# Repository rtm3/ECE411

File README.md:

ECE411 - T03
======

Group Design Project

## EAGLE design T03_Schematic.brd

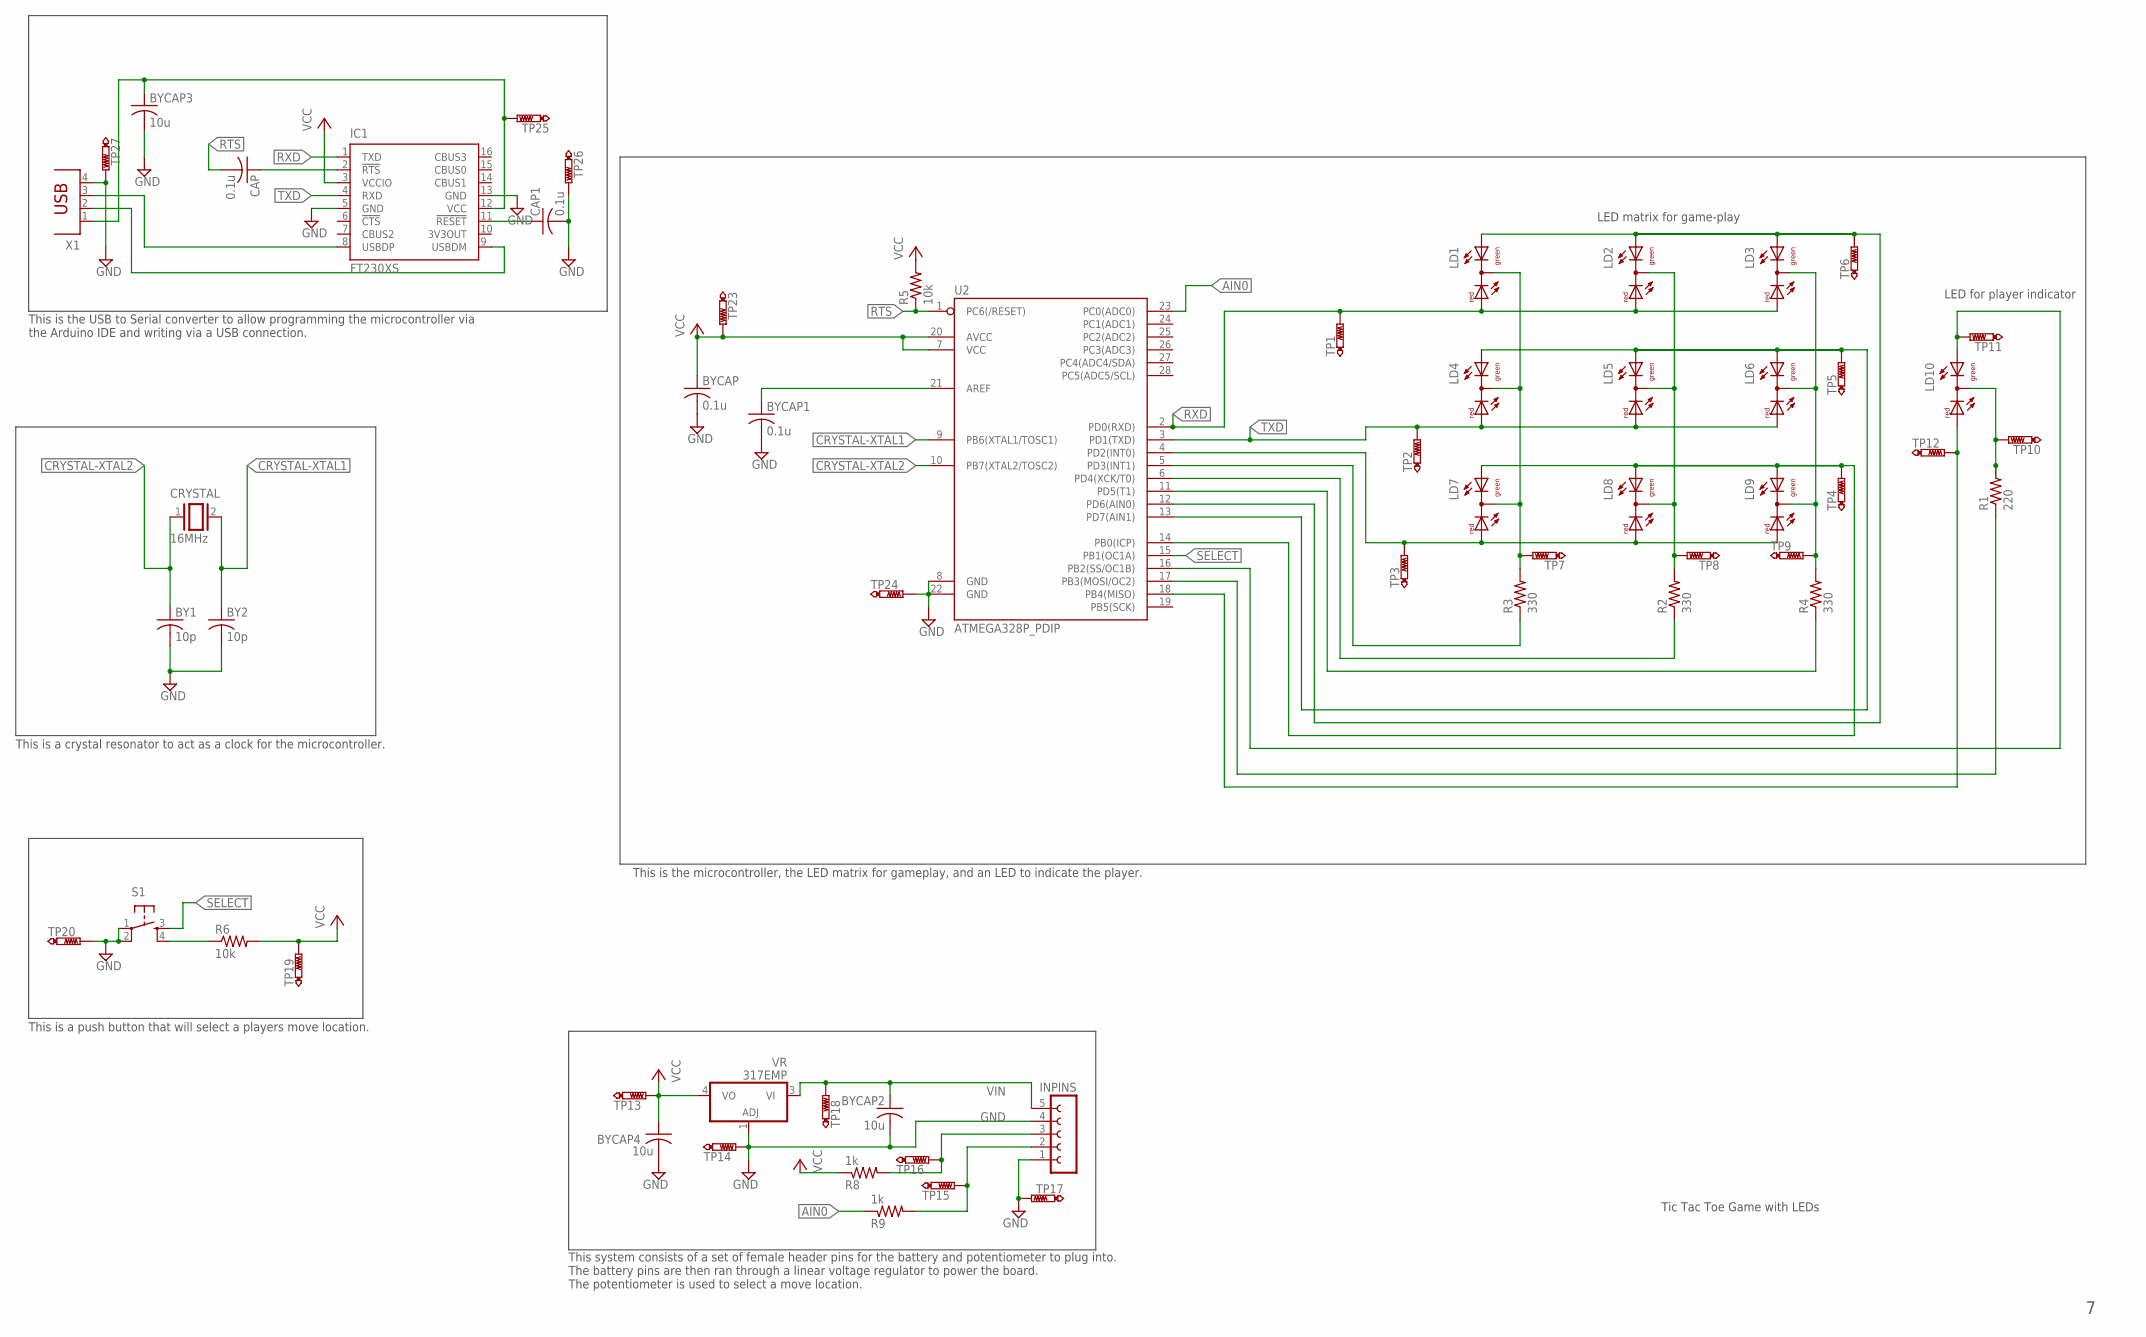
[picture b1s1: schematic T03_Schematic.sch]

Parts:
BY1, BY2: 10p; C0805
BYCAP, BYCAP1: 0.1u; C0805
BYCAP2, BYCAP3, BYCAP4: 10u; C0805
CAP, CAP1: 0.1u; C0805
CRYSTAL: 16MHz; QS
IC1: FT230XS; SSOP16
INPINS: FE05-1
LD1, LD2, LD3, LD4, LD5, LD6, LD7, LD8, LD9, LD10: DUOLED-RG-C; DUOLED-C-5MM
R1: 220; M0805
R2, R3, R4: 330; M0805
R5, R6: 10k; M0805
R8, R9: 1k; M0805
S1: DTS-6
TP1, TP2, TP3, TP4, TP5, TP6, TP7, TP8, TP9, TP10, TP11, TP12, TP13, TP14, TP15, TP16, TP17, TP18, TP19, TP20, TP23, TP24, TP25, TP26, TP27: PTR1B1,27; B1,27
U2: ATMEGA328P_PDIP; DIL28-3
VR: 317EMP; SOT223
X1: PN61729

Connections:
AIN0: R9.1, U2.23 (PC0(ADC0))
CATH1: R3.1, U2.5 (PD3(INT1))
CATH2: R2.1, U2.6 (PD4(XCK/T0))
CATH3: R4.1, U2.11 (PD5(T1))
CATH4: R1.1, U2.17 (PB3(MOSI/OC2))
CRYSTAL-XTAL1: BY2.1, CRYSTAL.2, U2.9 (PB6(XTAL1/TOSC1))
CRYSTAL-XTAL2: BY1.1, CRYSTAL.1, U2.10 (PB7(XTAL2/TOSC2))
D+: IC1.8 (USBDP), X1.3
D-: IC1.9 (USBDM), X1.2
GND: BY1.2, BY2.2, BYCAP.2, BYCAP1.2, BYCAP2.2, BYCAP3.2, BYCAP4.2, CAP1.2, IC1.5 (GND), IC1.13 (GND), INPINS.1, INPINS.4, S1.1, S1.2, TP14.TP, TP17.TP, TP20.TP, TP24.TP, TP26.TP, TP27.TP, U2.8 (GND), U2.22 (GND), VR.1 (ADJ), X1.4
GREN1: LD1.AX (AG), LD2.AX (AG), LD3.AX (AG), TP6.TP, U2.12 (PD6(AIN0))
GREN2: LD4.AX (AG), LD5.AX (AG), LD6.AX (AG), TP5.TP, U2.13 (PD7(AIN1))
GREN3: LD7.AX (AG), LD8.AX (AG), LD9.AX (AG), TP4.TP, U2.14 (PB0(ICP))
unnamed: LD1.C, LD4.C, LD7.C, R3.2, TP7.TP
unnamed: R6.1, S1.4
unnamed: LD2.C, LD5.C, LD8.C, R2.2, TP8.TP
unnamed: CAP.1, IC1.2 (!RTS)
unnamed: LD3.C, LD6.C, LD9.C, R4.2, TP9.TP
unnamed: CAP1.1, IC1.11 (!RESET)
unnamed: BYCAP1.1, U2.21 (AREF)
unnamed: LD10.C, R1.2, TP10.TP
PLAY1: LD10.AX (AG), TP11.TP, U2.16 (PB2(SS/OC1B))
PLAY2: LD10.AR, TP12.TP, U2.18 (PB4(MISO))
RED3: LD7.AR, LD8.AR, LD9.AR, TP3.TP, U2.4 (PD2(INT0))
RTS: CAP.2, R5.1, U2.1 (PC6(/RESET))
RXD: IC1.1 (TXD), LD1.AR, LD2.AR, LD3.AR, TP1.TP, U2.2 (PD0(RXD))
SELECT: S1.3, U2.15 (PB1(OC1A))
SELECTPIN: INPINS.2, R9.2, TP15.TP
TXD: IC1.4 (RXD), LD4.AR, LD5.AR, LD6.AR, TP2.TP, U2.3 (PD1(TXD))
USBVCC: BYCAP3.1, IC1.12 (VCC), TP25.TP, X1.1
V+POT: INPINS.3, R8.2, TP16.TP
VCC: BYCAP.1, BYCAP4.1, IC1.3 (VCCIO), R5.2, R6.2, R8.1, TP13.TP, TP19.TP, TP23.TP, U2.7 (VCC), U2.20 (AVCC), VR.4 (VO)
VIN: BYCAP2.1, INPINS.5, TP18.TP, VR.3 (VI)

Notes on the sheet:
LED matrix for game-play
LED for player indicator
Tic Tac Toe Game with LEDs
This system consists of a set of female header pins for the battery and potentiometer to plug into. The battery pins are then ran through a linear voltage regulator to power the board. The potentiometer is used to select a move location.
This is a push button that will select a players move location.
This is a crystal resonator to act as a clock for the microcontroller.
This is the USB to Serial converter to allow programming the microcontroller via the Arduino IDE and writing via a USB connection.
This is the microcontroller, the LED matrix for gameplay, and an LED to indicate the player.

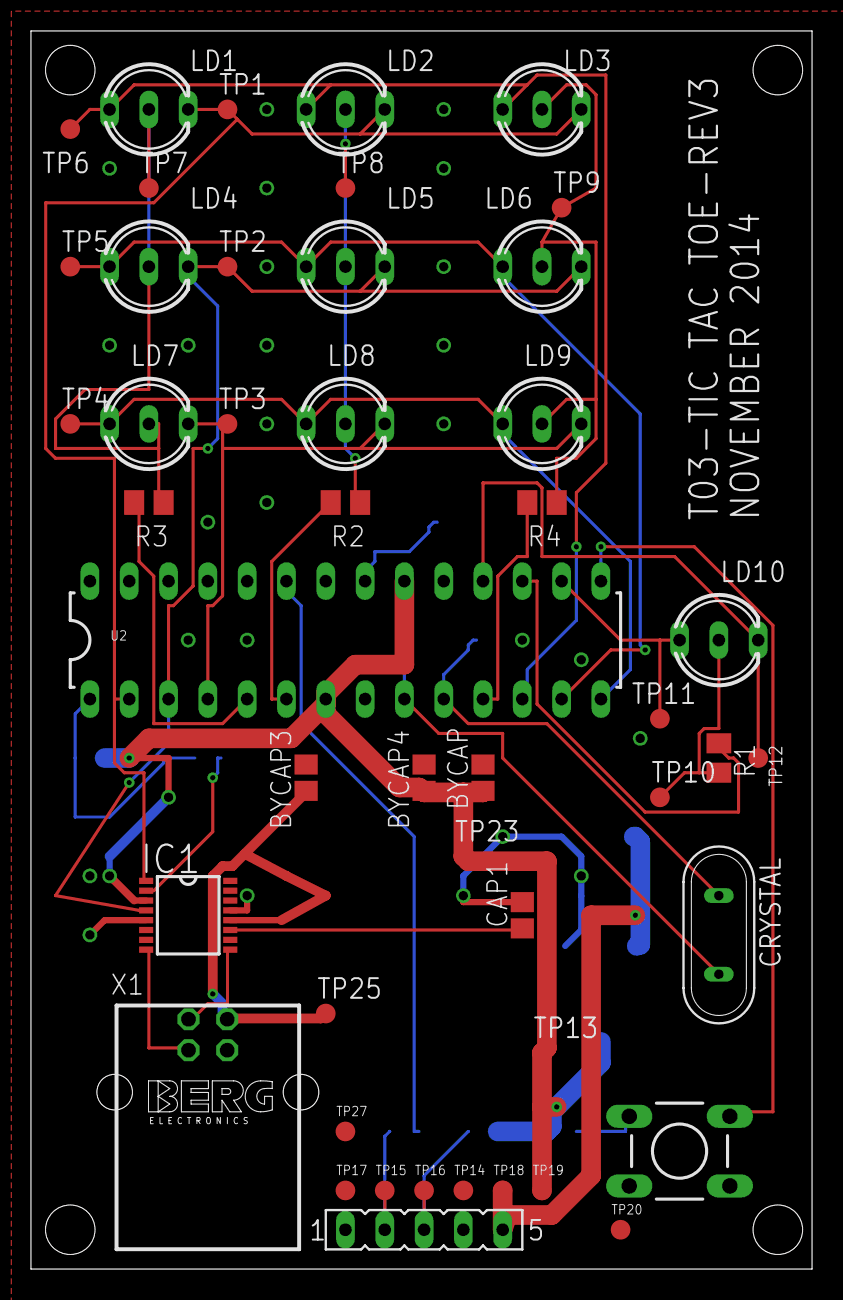
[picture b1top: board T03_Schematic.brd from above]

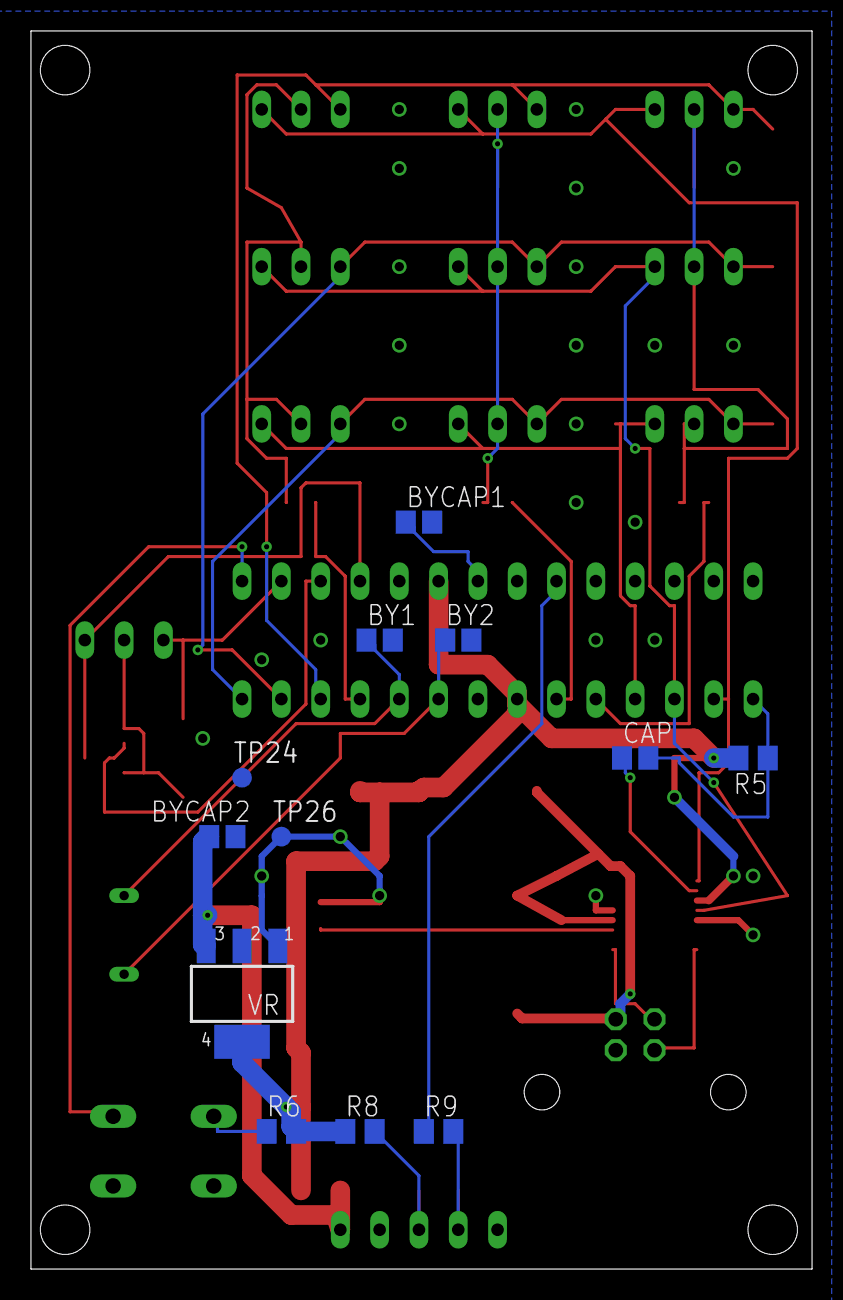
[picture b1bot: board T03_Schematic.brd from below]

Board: 2 copper layers, 50.5 x 80.0 mm, 59 parts (12 on the bottom side), 33 nets.

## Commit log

2014-10-22 Add of program developed so far
2014-10-23 HW #2, Project Proposal
2014-10-24 Create Requirements
2014-10-26 Sam's version of the requirements
2014-10-27 Homework #3: Requirements
2014-10-27 Initial Bill Of Materials to help with the schematic
2014-10-28 bom for Sam to use while creating schematic picture of prototype
2014-10-28 Change readme to show team number
2014-10-28 small changes in the spreadsheet formatting
2014-10-29 this is a picture of the schematic so far
2014-10-29 Try opening this file on your eaglecad
2014-10-29 newer version ELC error free
2014-11-02 Renamed files to proper format
2014-11-04 deleted old schem pic
2014-11-04 rev 2 of schematic
2014-11-04 rev 3
2014-11-05 rev 4
2014-11-05 Added values to components
2014-11-05 Input pins and voltage regulator added. Rev 6
2014-11-05 Test points added to schematic, board created
2014-11-09 Schematic has usb, new board
2014-11-10 final layout and schematic
2014-11-10 Project schedule - task view and gantt chart
2014-11-19 System model added
2014-11-25 Homework 6 added
2014-12-11 Added final code
2014-12-11 Weekly Check-ins

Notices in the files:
parts and their libraries:
SparkFun-DigitalIC: Licensing: Creative Commons ShareAlike 4.0 International - https://creativecommons.org/licenses/by-sa/4.0
